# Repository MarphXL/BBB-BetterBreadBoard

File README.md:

# B³ - BetterBreadBoard
## Inhaltsverzeichnis
1. [x] [Inhaltsverzeichnis](#Inhaltsverzeichnis)
1. [x] [Beschreibung](#Beschreibung)
1. [x] [Hardware](#Hardware)
   1. [x] [Technische Daten](#technische-daten)
   1. [x] [Datasheet](#datasheet)
   1. [x] [PCB](#PCB)
1. [x] [Software](#Software)
1. [x] [3D](#3D)
1. [x] [Where to buy](#Where-to-buy)
1. [ ] [Abbildungen](#Abbildungen)
1. [x] [Credits](#Credits)

## Beschreibung
Breadboards from china are often very very low quality. So this is a breadboard on my own pcb. I have designed some adapters for different arduino-versions, so I can easily contact them on the breadboard. The board separates serial, spi and I²C-Interfaces. At the top-right I can plug in an OLED-Display easyily.
3.3V comes from an AMS1117. So if something went wrong or I've new ideas it might be, that I make a better version.

## Hardware
### Technische Daten
* 400 pins (200 pins each side) to work with
* 40 GND- and 40 Power-pins at the top and at the bottom
* some LED, Poti, Switches, one encoder and one  buzzer
* Jumper to switch between 5V from USB-C-Connector or from the Microcontroller

### Datasheet
./.

### PCB
* [Adapters](PCB/Adapters)
* [B³ - BetterBreadBoard](PCB)

## Software
./.

## 3D
./.

## Where to buy
./.

## Abbildungen
* 
* 
* 
* 

## Credits
* :+1: [arduino](https://github.com/arduino)
* :+1: [adafruit](https://github.com/adafruit)
* :+1: [sparkfun](https://github.com/sparkfun)
* :+1: [Watterott](https://github.com/watterott) and @awatterott for great SW, HW and products
* :+1: [atom](https://github.com/atom)
* :+1: [mattahan](https://www.deviantart.com/mattahan) for the [Buuf graphics](https://www.deviantart.com/mattahan/art/Buuf-37966044)
* :+1: @ikatyang for the [emoji-cheat-sheet](https://github.com/ikatyang/emoji-cheat-sheet/blob/master/README.md)

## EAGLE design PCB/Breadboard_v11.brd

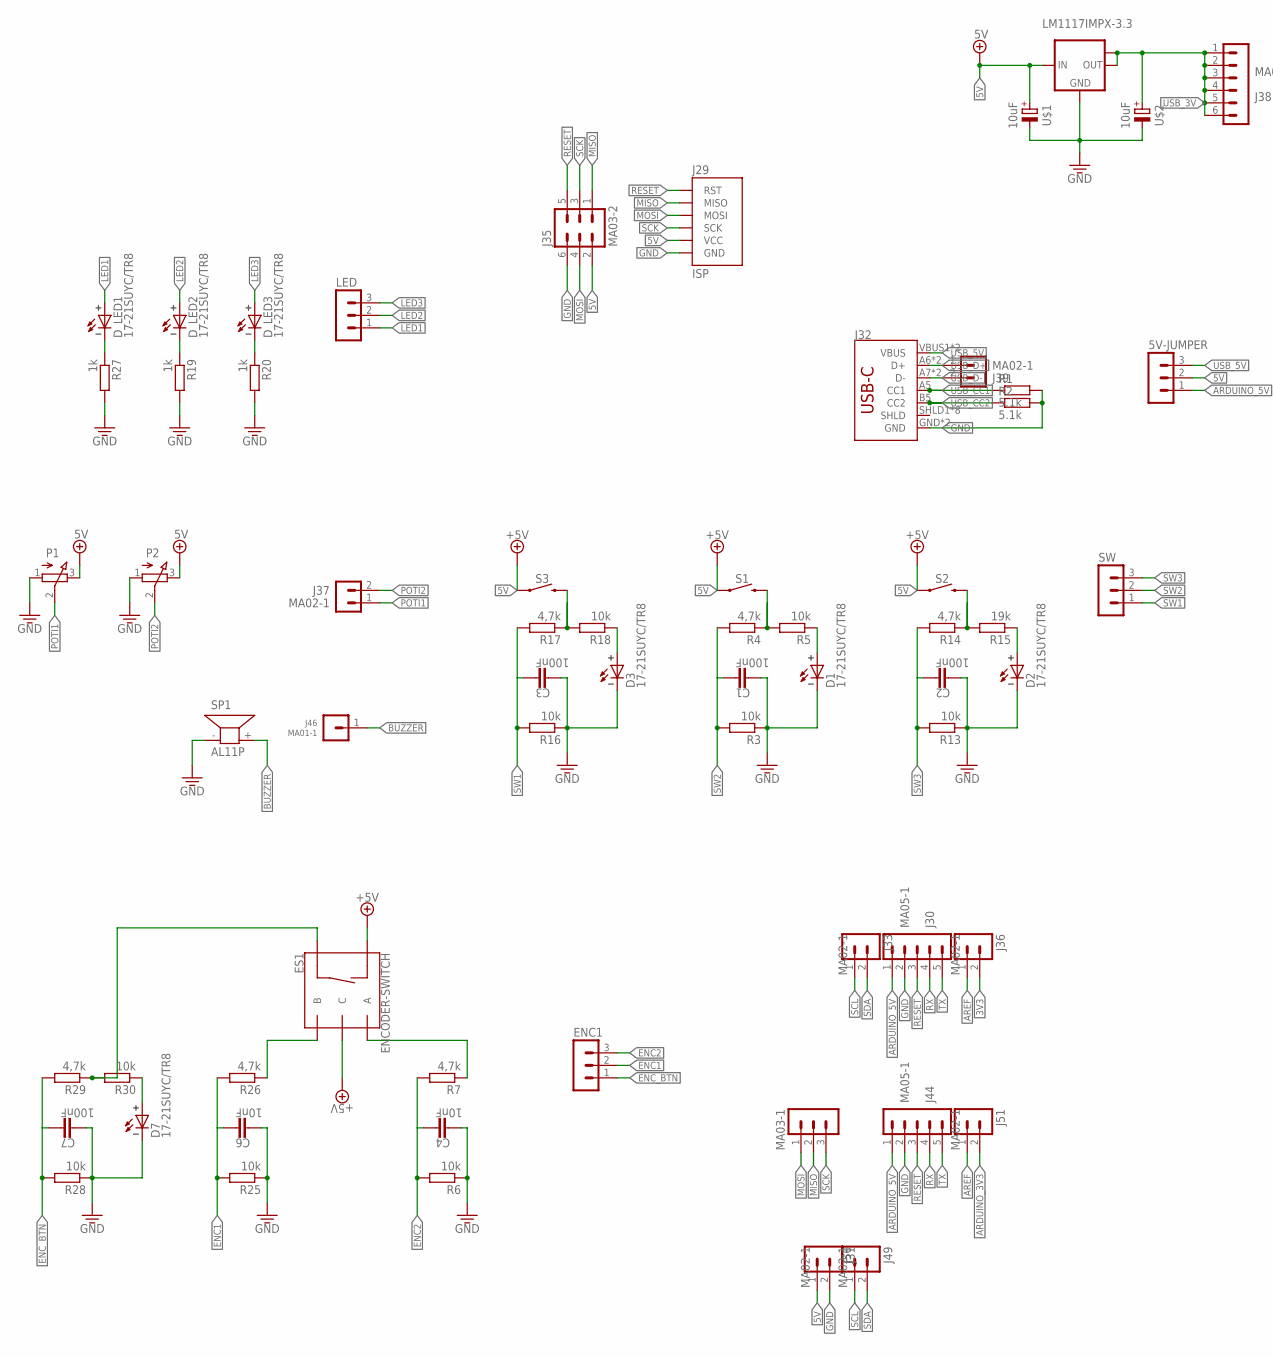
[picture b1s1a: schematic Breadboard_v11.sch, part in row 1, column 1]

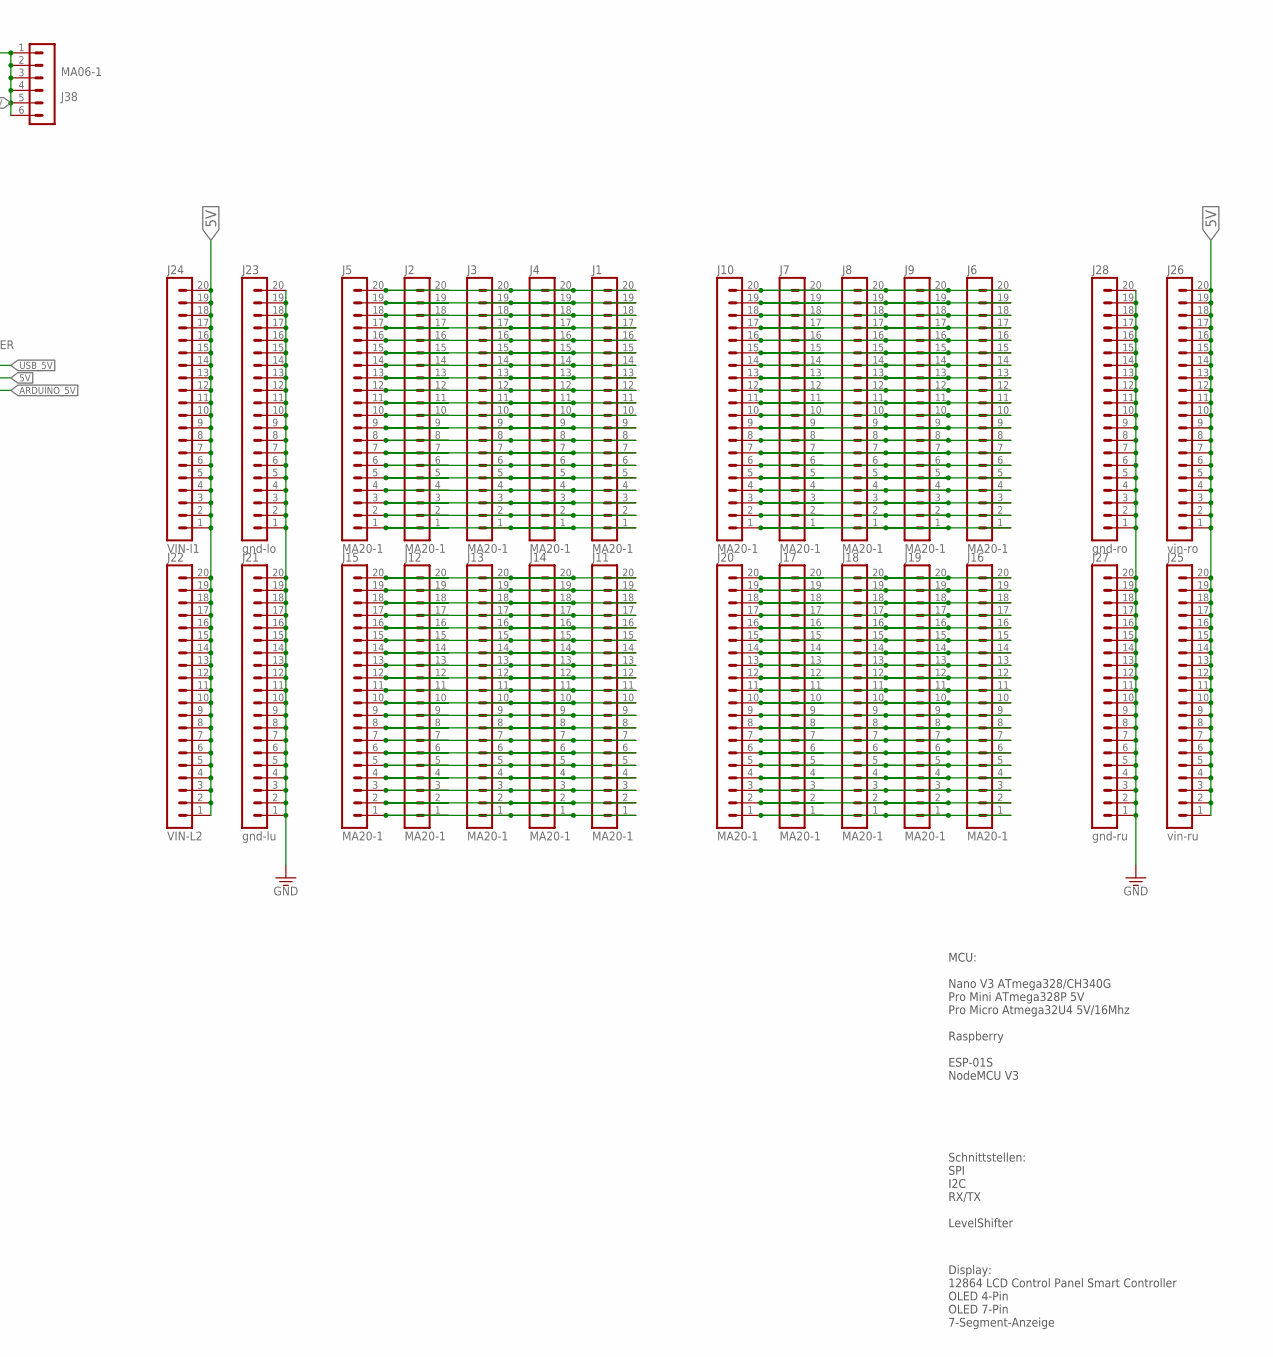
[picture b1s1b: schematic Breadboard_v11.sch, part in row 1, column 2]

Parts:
5V-JUMPER: MA03-1
C1, C2, C3, C7: 100nF; C0805
C4, C6: 10nF; C0805
D1, D2, D3, D7: 17-21SUYC/TR8; LED_3MM
D_LED1, D_LED2, D_LED3: 17-21SUYC/TR8; LED_3MM
ENC1: MA03-1
ES1: ENCODER-SWITCH; ROTARY_ENC_PLAIN
IC2: LM1117IMPX-3.3; SOT223
J1, J2, J3, J4, J5, J6, J7, J8, J9, J10, J11, J12, J13, J14, J15, J16, J17, J18, J19, J20: MA20-1
J21: gnd-lu; MA20-1
J22: VIN-L2; MA20-1
J23: gnd-lo; MA20-1
J24: VIN-l1; MA20-1
J25: vin-ru; MA20-1
J26: vin-ro; MA20-1
J27: gnd-ru; MA20-1
J28: gnd-ro; MA20-1
J29: ISP; ISP-2X3
J30, J44: MA05-1
J31, J33, J36, J37, J39, J49, J51: MA02-1
J32: USB_C16PIN; USB-C-16P
J35: MA03-2
J38: MA06-1
J46: MA01-1
J50: MA03-1
LED: MA03-1
P1, P2: 3RP/1610N
R1, R2: 5.1k; R0805
R3, R5, R6, R13, R16, R18, R25, R28, R30: 10k; R0805
R4, R7, R14, R17, R26, R29: 4,7k; R0805
R15: 19k; R0805
R19, R20, R27: 1k; R0805
S1, S2, S3: MOMENTARY-SWITCH-SPST-PTH-12MM; TACTILE_SWITCH_PTH_12MM
SP1: AL11P
SW: MA03-1
U$1, U$2: 10uF; C3216

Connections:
3V3: J36.2
5V: 5V-JUMPER.2, ES1.C, ES1.SW-, IC2.3 (IN), J22.1, J22.2, J22.3, J22.4, J22.5, J22.6, J22.7, J22.8, J22.9, J22.10, J22.11, J22.12, J22.13, J22.14, J22.15, J22.16, J22.17, J22.18, J22.19, J22.20, J24.1, J24.2, J24.3, J24.4, J24.5, J24.6, J24.7, J24.8, J24.9, J24.10, J24.11, J24.12, J24.13, J24.14, J24.15, J24.16, J24.17, J24.18, J24.19, J24.20, J25.1, J25.2, J25.3, J25.4, J25.5, J25.6, J25.7, J25.8, J25.9, J25.10, J25.11, J25.12, J25.13, J25.14, J25.15, J25.16, J25.17, J25.18, J25.19, J25.20, J26.1, J26.2, J26.3, J26.4, J26.5, J26.6, J26.7, J26.8, J26.9, J26.10, J26.11, J26.12, J26.13, J26.14, J26.15, J26.16, J26.17, J26.18, J26.19, J26.20, J29.VCC, J31.1, J35.2, P1.3 (E), P2.3 (E), S1.1, S2.1, S3.1, U$1.1 (+)
ARDUINO_3V3: J51.2
ARDUINO_5V: 5V-JUMPER.1, J30.1, J44.1
AREF: J36.1, J51.1
BUZZER: J46.1, SP1.+ (2)
ENC1: C6.1, ENC1.2, R25.2, R26.2
ENC2: C4.1, ENC1.3, R6.2, R7.2
ENC_BTN: C7.1, ENC1.1, R28.2, R29.2
GND: C1.2, C2.2, C3.2, C4.2, C6.2, C7.2, D1.C, D2.C, D3.C, D7.C, IC2.1 (GND), J21.1, J21.2, J21.3, J21.4, J21.5, J21.6, J21.7, J21.8, J21.9, J21.10, J21.11, J21.12, J21.13, J21.14, J21.15, J21.16, J21.17, J21.18, J21.19, J21.20, J23.1, J23.2, J23.3, J23.4, J23.5, J23.6, J23.7, J23.8, J23.9, J23.10, J23.11, J23.12, J23.13, J23.14, J23.15, J23.16, J23.17, J23.18, J23.19, J23.20, J27.1, J27.2, J27.3, J27.4, J27.5, J27.6, J27.7, J27.8, J27.9, J27.10, J27.11, J27.12, J27.13, J27.14, J27.15, J27.16, J27.17, J27.18, J27.19, J27.20, J28.1, J28.2, J28.3, J28.4, J28.5, J28.6, J28.7, J28.8, J28.9, J28.10, J28.11, J28.12, J28.13, J28.14, J28.15, J28.16, J28.17, J28.18, J28.19, J28.20, J29.GND, J30.2, J31.2, J32.GND, J32.GND2 (GND), J35.6, J44.2, P1.1 (A), P2.1 (A), R1.2, R2.2, R3.1, R6.1, R13.1, R16.1, R19.2, R20.2, R25.1, R27.2, R28.1, SP1.- (1), U$1.2 (-), U$2.2 (-)
LED1: D_LED1.A, LED.1
LED2: D_LED2.A, LED.2
LED3: D_LED3.A, LED.3
LED+_$1: D1.A, R5.1
LED+_$2: D2.A, R15.1
LED+_$3: D3.A, R18.1
LED+_$7: D7.A, R30.1
MISO: J29.MISO, J35.1, J50.2
MOSI: J29.MOSI, J35.4, J50.1
unnamed: J1.1, J2.1, J3.1, J4.1, J5.1
unnamed: J1.2, J2.2, J3.2, J4.2, J5.2
unnamed: J1.3, J2.3, J3.3, J4.3, J5.3
unnamed: J1.4, J2.4, J3.4, J4.4, J5.4
unnamed: J1.5, J2.5, J3.5, J4.5, J5.5
unnamed: J1.6, J2.6, J3.6, J4.6, J5.6
unnamed: J1.7, J2.7, J3.7, J4.7, J5.7
unnamed: J1.8, J2.8, J3.8, J4.8, J5.8
unnamed: J1.9, J2.9, J3.9, J4.9, J5.9
unnamed: J1.10, J2.10, J3.10, J4.10, J5.10
unnamed: J1.11, J2.11, J3.11, J4.11, J5.11
unnamed: J1.12, J2.12, J3.12, J4.12, J5.12
unnamed: J1.13, J2.13, J3.13, J4.13, J5.13
unnamed: J1.14, J2.14, J3.14, J4.14, J5.14
unnamed: J1.15, J2.15, J3.15, J4.15, J5.15
unnamed: J1.16, J2.16, J3.16, J4.16, J5.16
unnamed: J1.17, J2.17, J3.17, J4.17, J5.17
unnamed: J1.18, J2.18, J3.18, J4.18, J5.18
unnamed: J1.19, J2.19, J3.19, J4.19, J5.19
unnamed: J1.20, J2.20, J3.20, J4.20, J5.20
unnamed: J6.1, J7.1, J8.1, J9.1, J10.1
unnamed: J6.2, J7.2, J8.2, J9.2, J10.2
unnamed: J6.3, J7.3, J8.3, J9.3, J10.3
unnamed: J6.4, J7.4, J8.4, J9.4, J10.4
unnamed: J6.5, J7.5, J8.5, J9.5, J10.5
unnamed: J6.6, J7.6, J8.6, J9.6, J10.6
unnamed: J6.7, J7.7, J8.7, J9.7, J10.7
unnamed: J6.8, J7.8, J8.8, J9.8, J10.8
unnamed: J6.9, J7.9, J8.9, J9.9, J10.9
unnamed: J6.10, J7.10, J8.10, J9.10, J10.10
unnamed: J6.11, J7.11, J8.11, J9.11, J10.11
unnamed: J6.12, J7.12, J8.12, J9.12, J10.12
unnamed: J6.13, J7.13, J8.13, J9.13, J10.13
unnamed: J6.14, J7.14, J8.14, J9.14, J10.14
unnamed: J6.15, J7.15, J8.15, J9.15, J10.15
unnamed: J6.16, J7.16, J8.16, J9.16, J10.16
unnamed: J6.17, J7.17, J8.17, J9.17, J10.17
unnamed: J6.18, J7.18, J8.18, J9.18, J10.18
unnamed: J6.19, J7.19, J8.19, J9.19, J10.19
unnamed: J6.20, J7.20, J8.20, J9.20, J10.20
unnamed: J11.1, J12.1, J13.1, J14.1, J15.1
unnamed: J11.2, J12.2, J13.2, J14.2, J15.2
unnamed: J11.3, J12.3, J13.3, J14.3, J15.3
unnamed: J11.4, J12.4, J13.4, J14.4, J15.4
unnamed: J11.5, J12.5, J13.5, J14.5, J15.5
unnamed: J11.6, J12.6, J13.6, J14.6, J15.6
unnamed: J11.7, J12.7, J13.7, J14.7, J15.7
unnamed: J11.8, J12.8, J13.8, J14.8, J15.8
unnamed: J11.9, J12.9, J13.9, J14.9, J15.9
unnamed: J11.10, J12.10, J13.10, J14.10, J15.10
unnamed: J11.11, J12.11, J13.11, J14.11, J15.11
unnamed: J11.12, J12.12, J13.12, J14.12, J15.12
unnamed: J11.13, J12.13, J13.13, J14.13, J15.13
unnamed: J11.14, J12.14, J13.14, J14.14, J15.14
unnamed: J11.15, J12.15, J13.15, J14.15, J15.15
unnamed: J11.16, J12.16, J13.16, J14.16, J15.16
unnamed: J11.17, J12.17, J13.17, J14.17, J15.17
unnamed: J11.18, J12.18, J13.18, J14.18, J15.18
unnamed: J11.19, J12.19, J13.19, J14.19, J15.19
unnamed: J11.20, J12.20, J13.20, J14.20, J15.20
unnamed: J16.1, J17.1, J18.1, J19.1, J20.1
unnamed: J16.2, J17.2, J18.2, J19.2, J20.2
unnamed: J16.3, J17.3, J18.3, J19.3, J20.3
unnamed: J16.4, J17.4, J18.4, J19.4, J20.4
unnamed: J16.5, J17.5, J18.5, J19.5, J20.5
unnamed: J16.6, J17.6, J18.6, J19.6, J20.6
unnamed: J16.7, J17.7, J18.7, J19.7, J20.7
unnamed: J16.8, J17.8, J18.8, J19.8, J20.8
unnamed: J16.9, J17.9, J18.9, J19.9, J20.9
unnamed: J16.10, J17.10, J18.10, J19.10, J20.10
unnamed: J16.11, J17.11, J18.11, J19.11, J20.11
unnamed: J16.12, J17.12, J18.12, J19.12, J20.12
unnamed: J16.13, J17.13, J18.13, J19.13, J20.13
unnamed: J16.14, J17.14, J18.14, J19.14, J20.14
unnamed: J16.15, J17.15, J18.15, J19.15, J20.15
unnamed: J16.16, J17.16, J18.16, J19.16, J20.16
unnamed: J16.17, J17.17, J18.17, J19.17, J20.17
unnamed: J16.18, J17.18, J18.18, J19.18, J20.18
unnamed: J16.19, J17.19, J18.19, J19.19, J20.19
unnamed: J16.20, J17.20, J18.20, J19.20, J20.20
unnamed: R4.1, R5.2, S1.3 (2)
unnamed: R14.1, R15.2, S2.3 (2)
unnamed: R17.1, R18.2, S3.3 (2)
unnamed: D_LED1.C, R27.1
unnamed: D_LED2.C, R19.1
unnamed: D_LED3.C, R20.1
unnamed: ES1.A, R7.1
unnamed: ES1.B, R26.1
unnamed: ES1.SW+, R29.1, R30.2
POTI1: J37.1, P1.2 (S)
POTI2: J37.2, P2.2 (S)
RESET: J29.RST, J30.3, J35.5, J44.3
RX: J30.4, J44.4
SCK: J29.SCK, J35.3, J50.3
SCL: J33.1, J49.1
SDA: J33.2, J49.2
SW1: C3.1, R16.2, R17.2, SW.1
SW2: C1.1, R3.2, R4.2, SW.2
SW3: C2.1, R13.2, R14.2, SW.3
TX: J30.5, J44.5
USB_3V: IC2.2 (OUT), IC2.TAB (OUT1), J38.1, J38.2, J38.3, J38.4, J38.5, J38.6, U$2.1 (+)
USB_5V: 5V-JUMPER.3, J32.VBUS1 (VBUS), J32.VBUS2 (VBUS)
USB_CC1: J32.A5 (CC1), R1.1
USB_CC2: J32.B5 (CC2), R2.1
USB_D+: J32.A6 (D+), J32.B6 (D+), J39.1
USB_D-: J32.A7 (D-), J32.B7 (D-), J39.2

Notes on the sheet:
MCU: Nano V3 ATmega328/CH340G Pro Mini ATmega328P 5V Pro Micro Atmega32U4 5V/16Mhz Raspberry ESP-01S NodeMCU V3
Schnittstellen: SPI I2C RX/TX LevelShifter
Display: 12864 LCD Control Panel Smart Controller OLED 4-Pin OLED 7-Pin 7-Segment-Anzeige

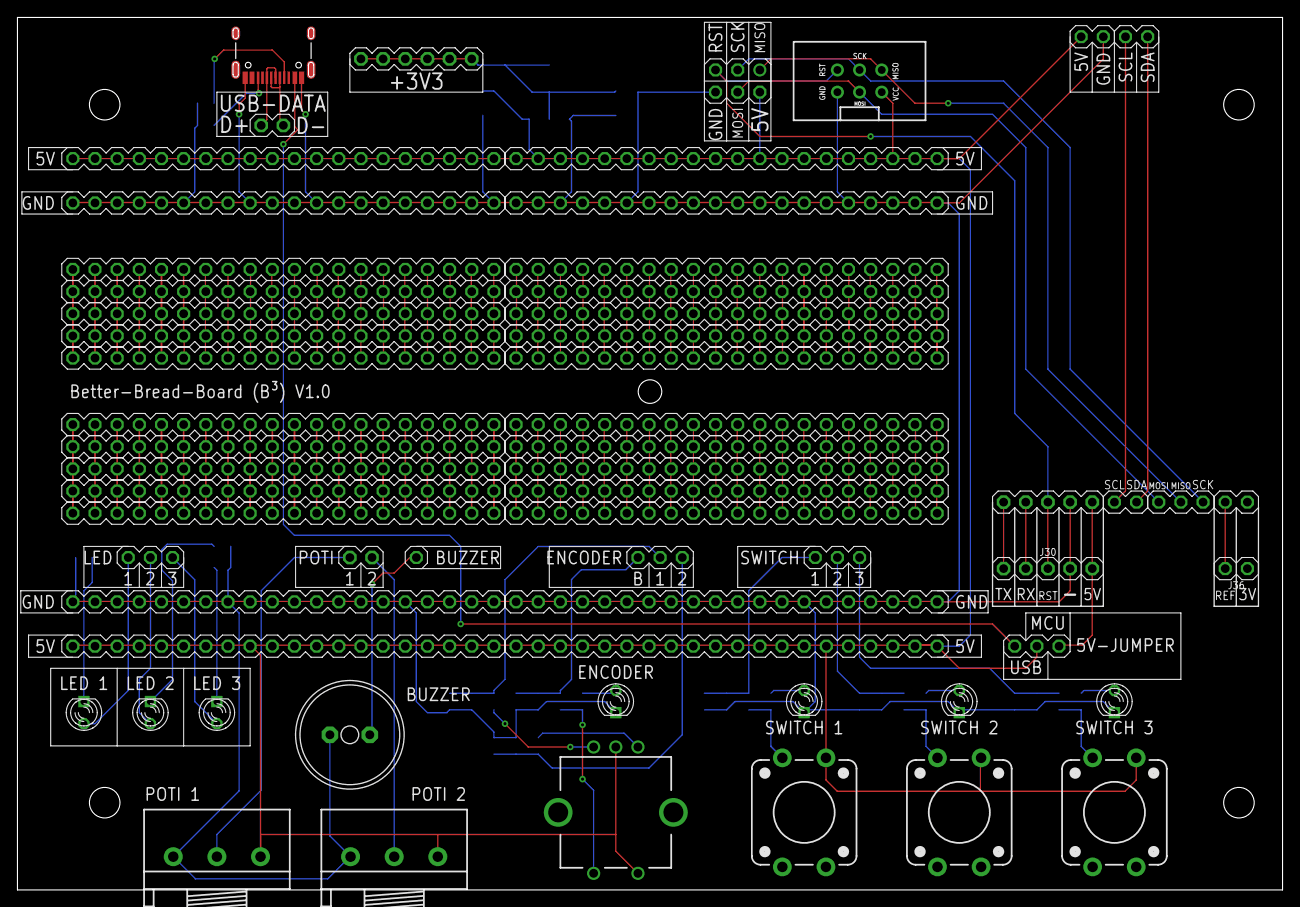
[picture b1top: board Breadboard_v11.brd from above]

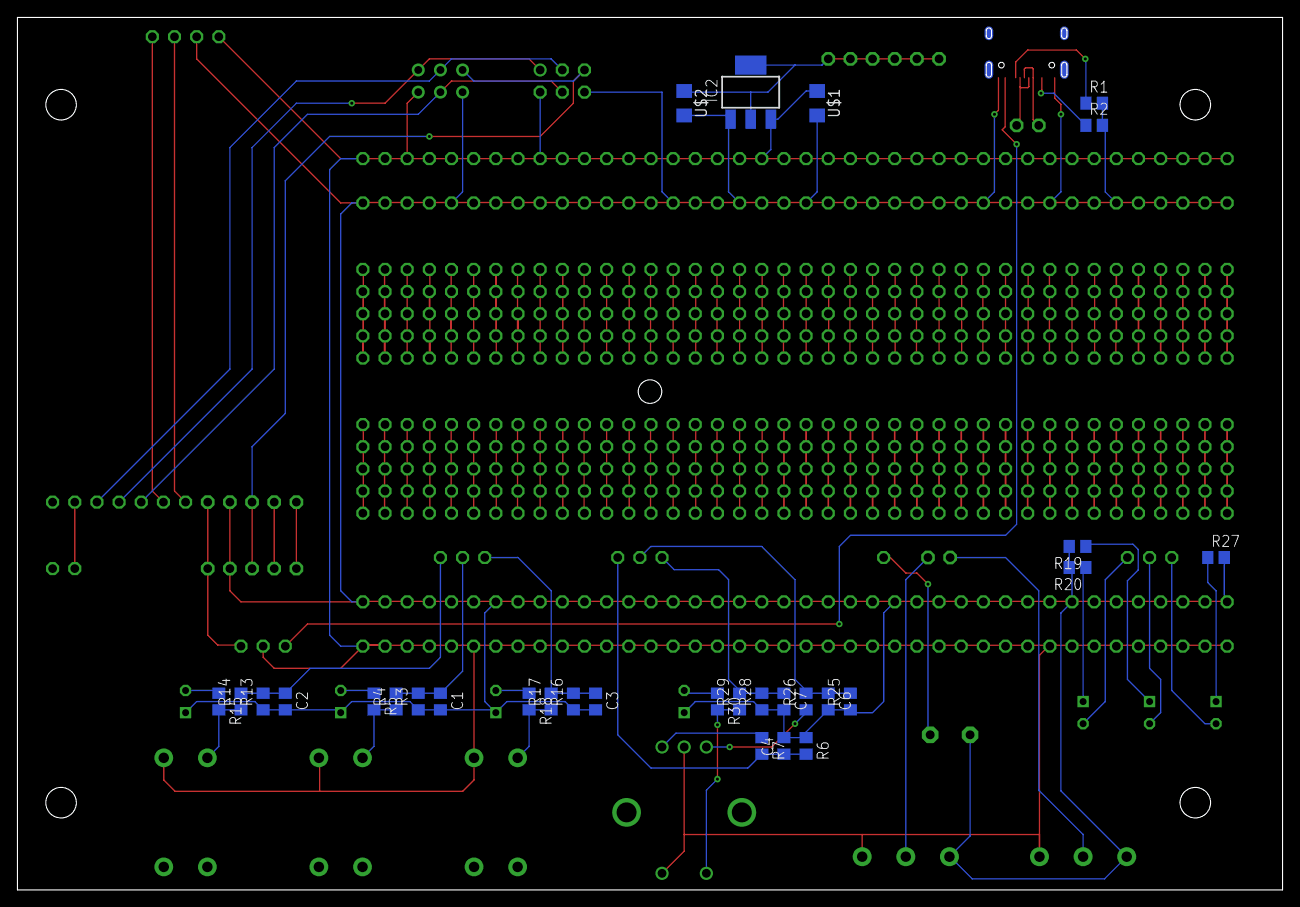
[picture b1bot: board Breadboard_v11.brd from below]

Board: 2 copper layers, 145.0 x 100.0 mm, 91 parts (30 on the bottom side), 123 nets.

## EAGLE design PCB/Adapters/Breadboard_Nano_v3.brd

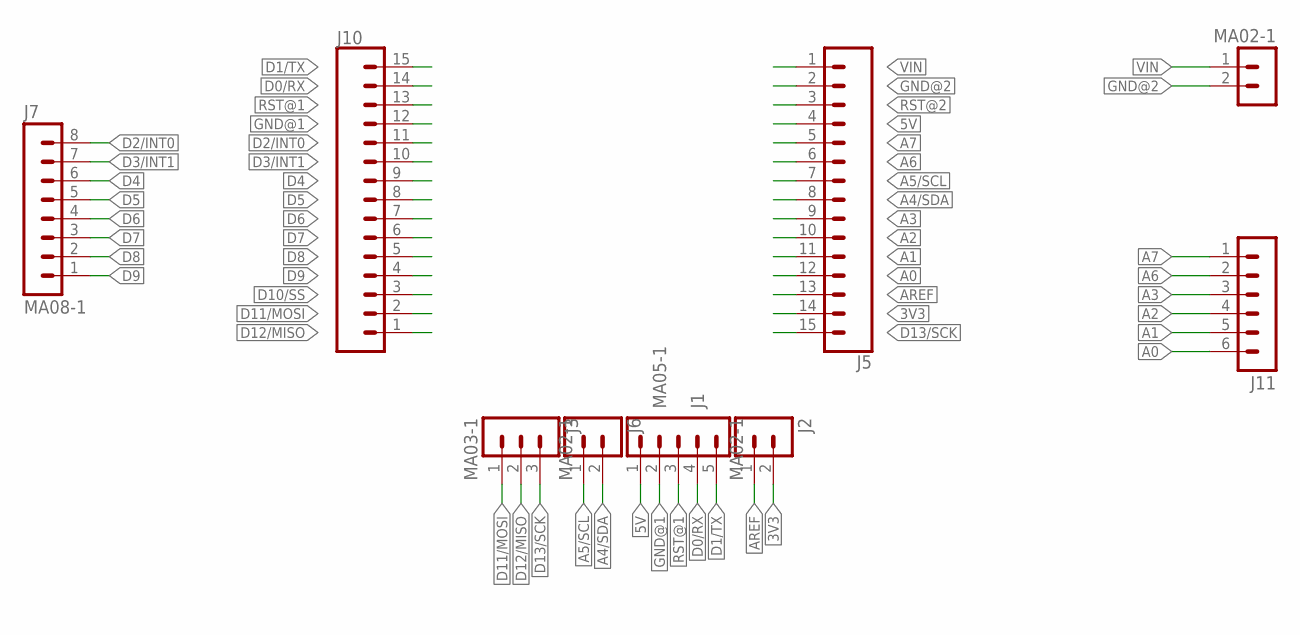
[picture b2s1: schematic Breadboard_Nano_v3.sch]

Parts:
J1: MA05-1
J2, J6, J9: MA02-1
J3: MA03-1
J5, J10: CONN_15; 1X15
J7: MA08-1
J11: MA06-1

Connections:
3V3: J2.2, J5.14
5V: J1.1, J5.4
A0: J5.12, J11.6
A1: J5.11, J11.5
A2: J5.10, J11.4
A3: J5.9, J11.3
A4/SDA: J5.8, J6.2
A5/SCL: J5.7, J6.1
A6: J5.6, J11.2
A7: J5.5, J11.1
AREF: J2.1, J5.13
D0/RX: J1.4, J10.14
D1/TX: J1.5, J10.15
D2/INT0: J7.8, J10.11
D3/INT1: J7.7, J10.10
D4: J7.6, J10.9
D5: J7.5, J10.8
D6: J7.4, J10.7
D7: J7.3, J10.6
D8: J7.2, J10.5
D9: J7.1, J10.4
D10/SS: J10.3
D11/MOSI: J3.1, J10.2
D12/MISO: J3.2, J10.1
D13/SCK: J3.3, J5.15
GND@1: J1.2, J10.12
GND@2: J5.2, J9.2
RST@1: J1.3, J10.13
RST@2: J5.3
VIN: J5.1, J9.1

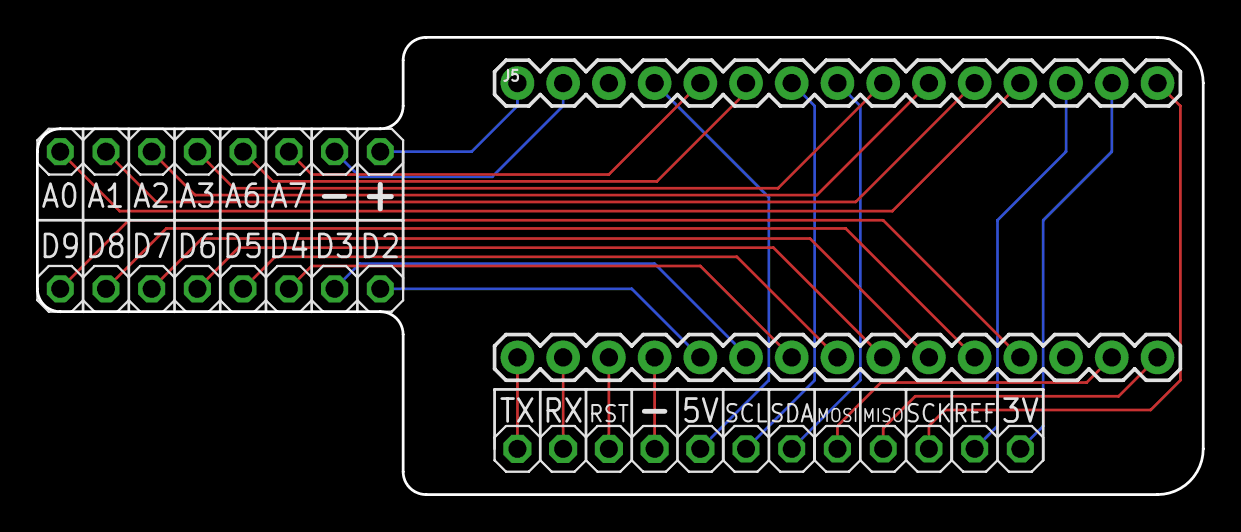
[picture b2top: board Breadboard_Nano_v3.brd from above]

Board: 2 copper layers, 64.8 x 25.4 mm, 9 parts (0 on the bottom side), 28 nets.

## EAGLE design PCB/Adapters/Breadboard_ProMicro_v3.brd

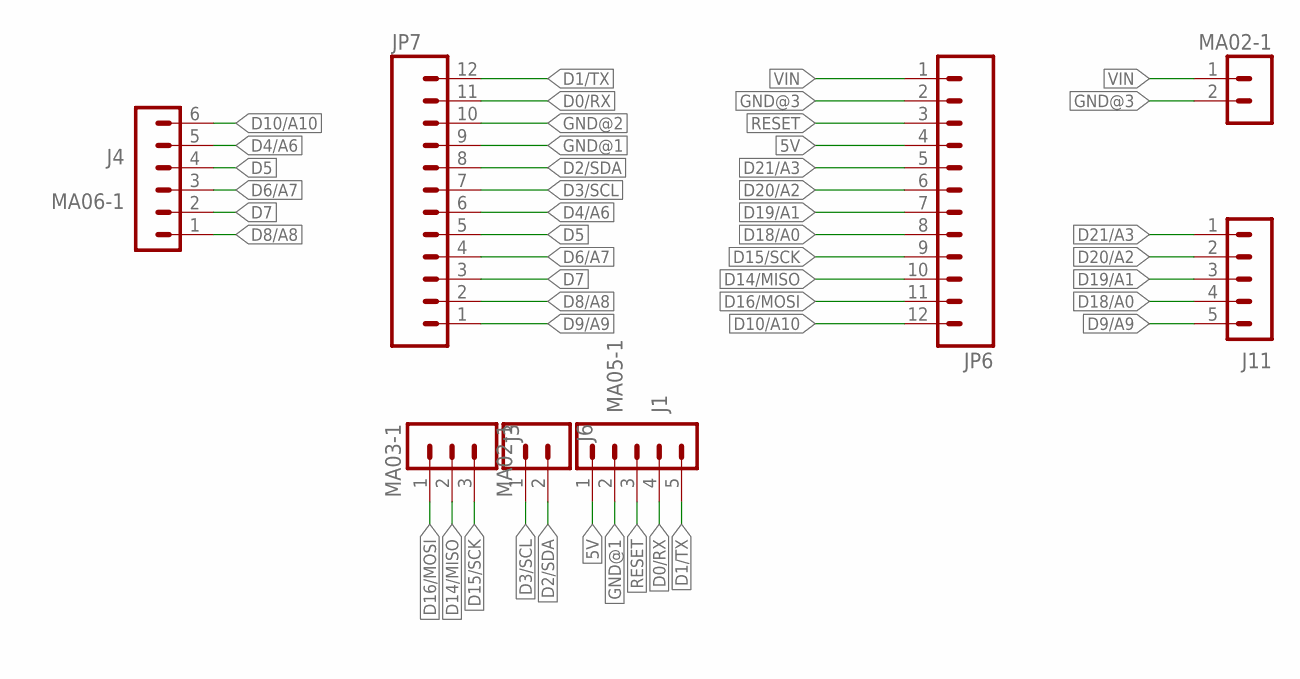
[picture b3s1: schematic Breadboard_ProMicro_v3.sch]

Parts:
J1, J11: MA05-1
J3: MA03-1
J4: MA06-1
J6, J9: MA02-1
JP6, JP7: M12PTH; 1X12

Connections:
5V: J1.1, JP6.4
D0/RX: J1.4, JP7.11
D1/TX: J1.5, JP7.12
D2/SDA: J6.2, JP7.8
D3/SCL: J6.1, JP7.7
D4/A6: J4.5, JP7.6
D5: J4.4, JP7.5
D6/A7: J4.3, JP7.4
D7: J4.2, JP7.3
D8/A8: J4.1, JP7.2
D9/A9: J11.5, JP7.1
D10/A10: J4.6, JP6.12
D14/MISO: J3.2, JP6.10
D15/SCK: J3.3, JP6.9
D16/MOSI: J3.1, JP6.11
D18/A0: J11.4, JP6.8
D19/A1: J11.3, JP6.7
D20/A2: J11.2, JP6.6
D21/A3: J11.1, JP6.5
GND@1: J1.2, JP7.9
GND@2: JP7.10
GND@3: J9.2, JP6.2
RESET: J1.3, JP6.3
VIN: J9.1, JP6.1

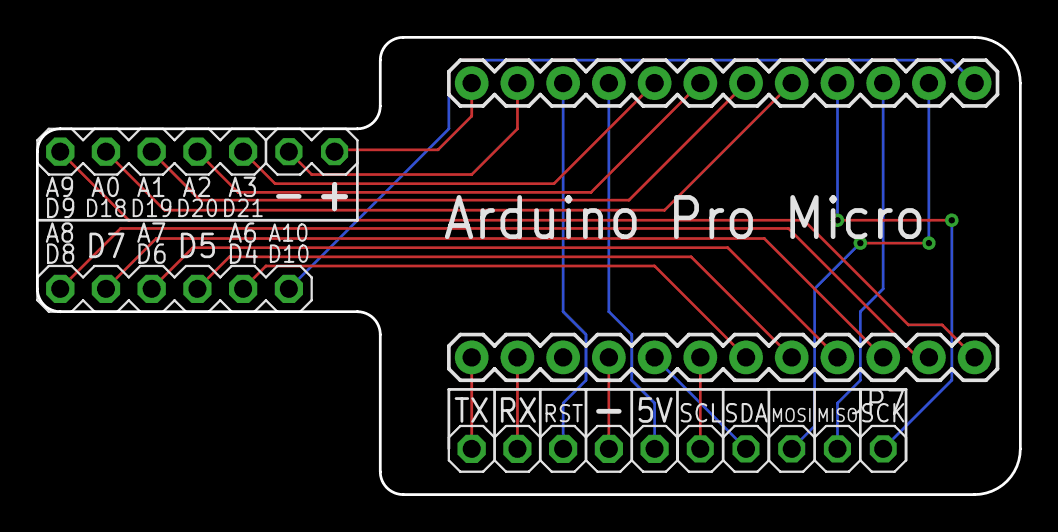
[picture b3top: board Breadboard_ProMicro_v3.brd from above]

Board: 2 copper layers, 54.6 x 25.4 mm, 8 parts (0 on the bottom side), 23 nets.

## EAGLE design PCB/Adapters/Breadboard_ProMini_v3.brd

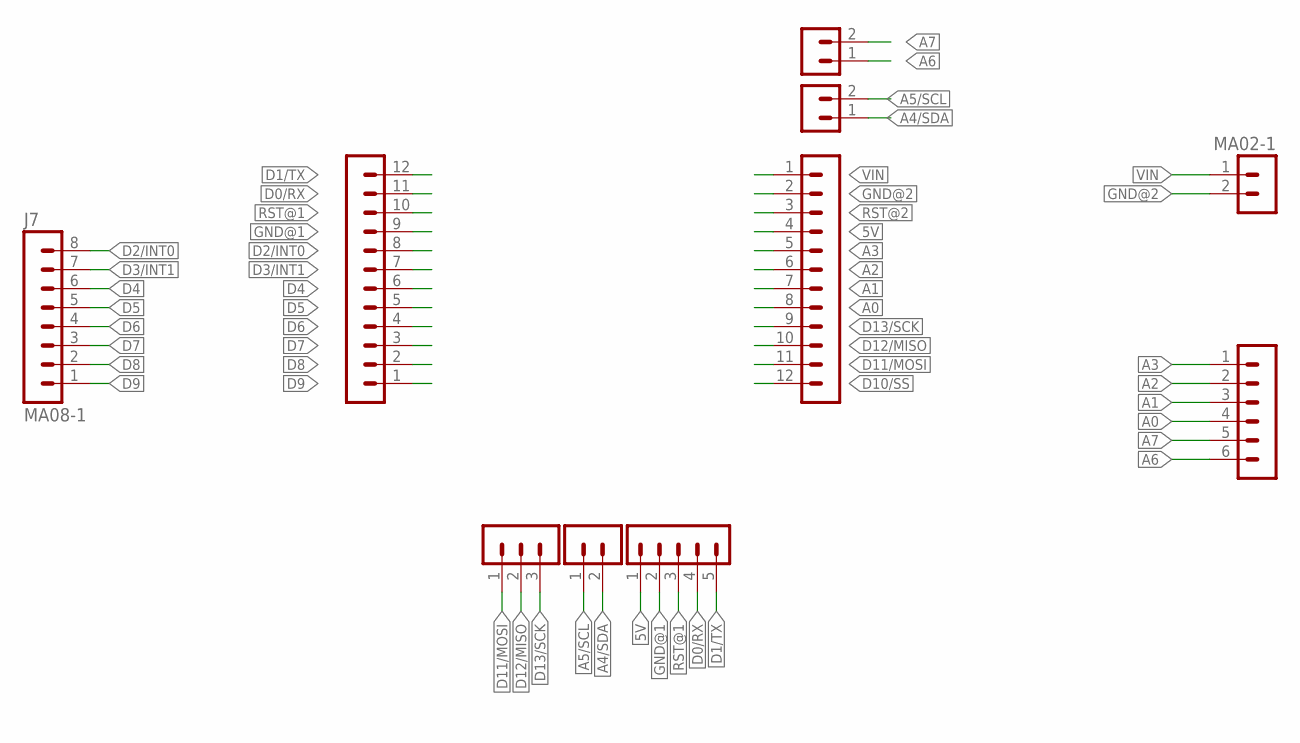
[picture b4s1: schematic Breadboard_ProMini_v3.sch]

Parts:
J1: MA05-1
J3: MA03-1
J4, J8: MA12-1
J5, J6, J9, J10: MA02-1
J7: MA08-1
J11: MA06-1

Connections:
5V: J1.1, J8.4
A0: J8.8, J11.4
A1: J8.7, J11.3
A2: J8.6, J11.2
A3: J8.5, J11.1
A4/SDA: J6.2, J10.1
A5/SCL: J6.1, J10.2
A6: J5.1, J11.6
A7: J5.2, J11.5
D0/RX: J1.4, J4.11
D1/TX: J1.5, J4.12
D2/INT0: J4.8, J7.8
D3/INT1: J4.7, J7.7
D4: J4.6, J7.6
D5: J4.5, J7.5
D6: J4.4, J7.4
D7: J4.3, J7.3
D8: J4.2, J7.2
D9: J4.1, J7.1
D10/SS: J8.12
D11/MOSI: J3.1, J8.11
D12/MISO: J3.2, J8.10
D13/SCK: J3.3, J8.9
GND@1: J1.2, J4.9
GND@2: J8.2, J9.2
RST@1: J1.3, J4.10
RST@2: J8.3
VIN: J8.1, J9.1

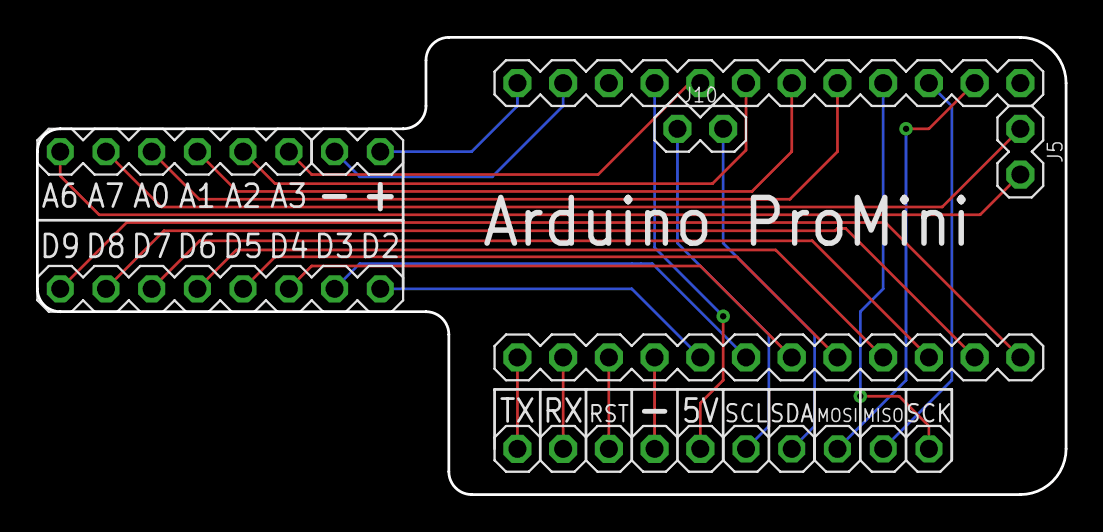
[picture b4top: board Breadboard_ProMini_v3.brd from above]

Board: 2 copper layers, 57.1 x 25.4 mm, 10 parts (0 on the bottom side), 26 nets.

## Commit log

2020-09-16 Create bla

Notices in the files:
parts and their libraries:
00_marph_CON1: Licensing: Creative Commons ShareAlike 4.0 International - https://creativecommons.org/licenses/by-sa/4.0
